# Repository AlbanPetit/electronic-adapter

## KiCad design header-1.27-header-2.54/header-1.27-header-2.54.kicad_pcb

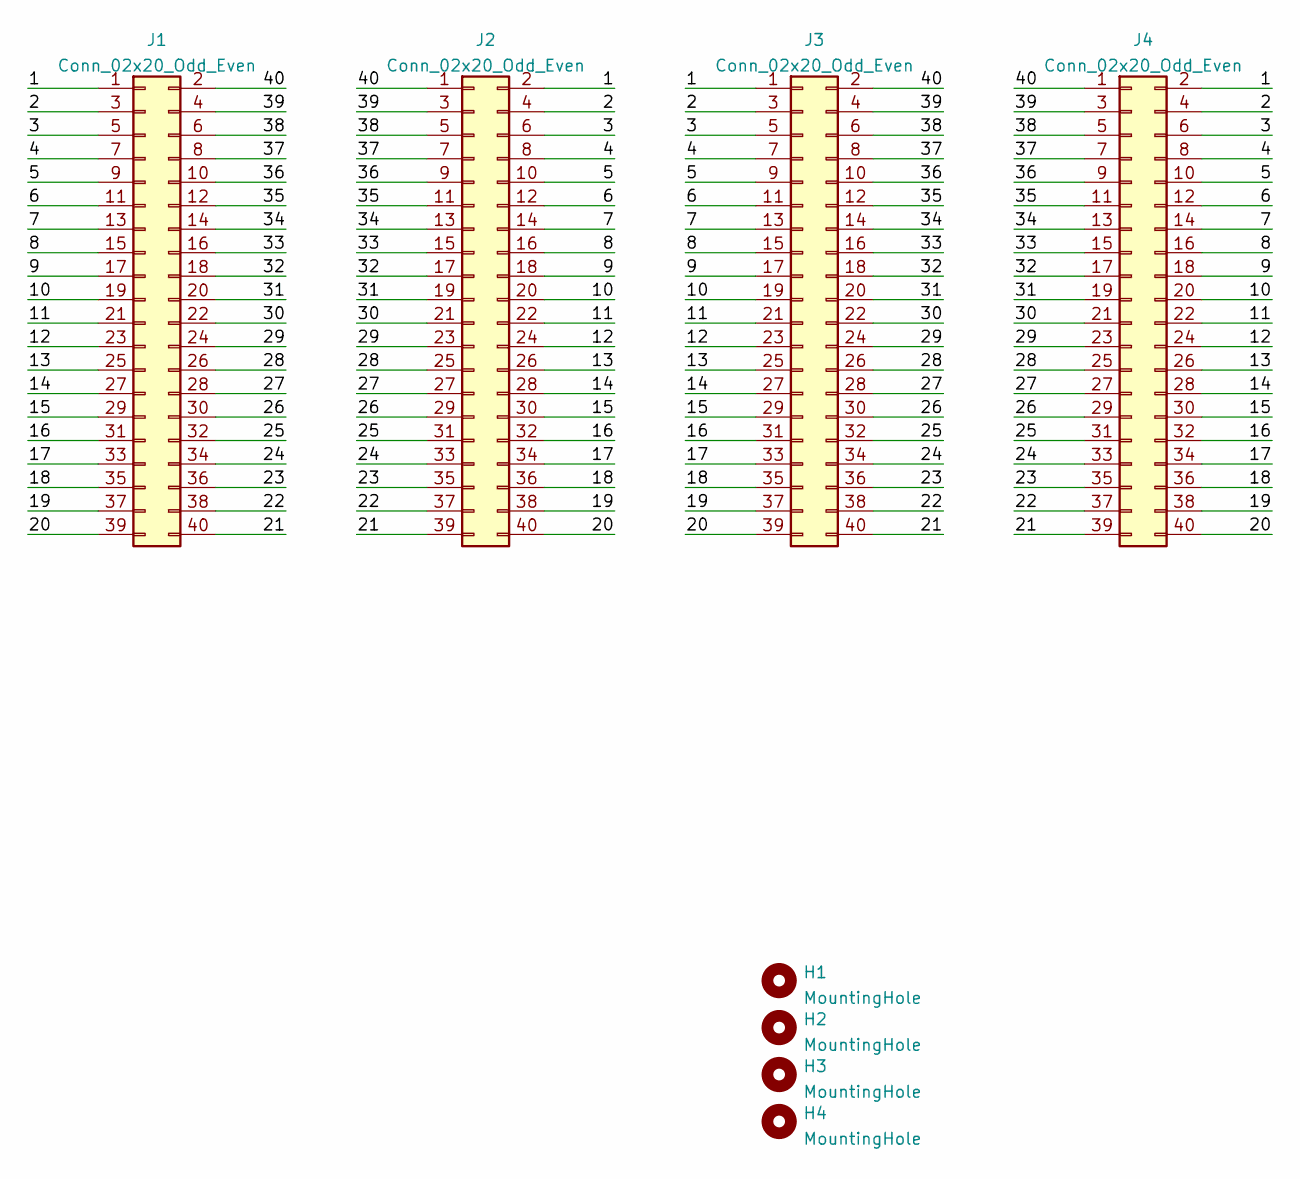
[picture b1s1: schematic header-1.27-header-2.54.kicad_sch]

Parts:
H1, H2, H3, H4: MountingHole; MountingHole_2.2mm_M2_DIN965_Pad
J1, J2: Conn_02x20_Odd_Even; PinHeader_2x20_P2.54mm_Vertical_SMD
J3, J4: Conn_02x20_Odd_Even; PinHeader_2x20_P1.27mm_Vertical_SMD

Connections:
/1: J1.1, J2.2, J3.1, J4.2
/2: J1.3, J2.4, J3.3, J4.4
/3: J1.5, J2.6, J3.5, J4.6
/4: J1.7, J2.8, J3.7, J4.8
/5: J1.9, J2.10, J3.9, J4.10
/6: J1.11, J2.12, J3.11, J4.12
/7: J1.13, J2.14, J3.13, J4.14
/8: J1.15, J2.16, J3.15, J4.16
/9: J1.17, J2.18, J3.17, J4.18
/10: J1.19, J2.20, J3.19, J4.20
/11: J1.21, J2.22, J3.21, J4.22
/12: J1.23, J2.24, J3.23, J4.24
/13: J1.25, J2.26, J3.25, J4.26
/14: J1.27, J2.28, J3.27, J4.28
/15: J1.29, J2.30, J3.29, J4.30
/16: J1.31, J2.32, J3.31, J4.32
/17: J1.33, J2.34, J3.33, J4.34
/18: J1.35, J2.36, J3.35, J4.36
/19: J1.37, J2.38, J3.37, J4.38
/20: J1.39, J2.40, J3.39, J4.40
/21: J1.40, J2.39, J3.40, J4.39
/22: J1.38, J2.37, J3.38, J4.37
/23: J1.36, J2.35, J3.36, J4.35
/24: J1.34, J2.33, J3.34, J4.33
/25: J1.32, J2.31, J3.32, J4.31
/26: J1.30, J2.29, J3.30, J4.29
/27: J1.28, J2.27, J3.28, J4.27
/28: J1.26, J2.25, J3.26, J4.25
/29: J1.24, J2.23, J3.24, J4.23
/30: J1.22, J2.21, J3.22, J4.21
/31: J1.20, J2.19, J3.20, J4.19
/32: J1.18, J2.17, J3.18, J4.17
/33: J1.16, J2.15, J3.16, J4.15
/34: J1.14, J2.13, J3.14, J4.13
/35: J1.12, J2.11, J3.12, J4.11
/36: J1.10, J2.9, J3.10, J4.9
/37: J1.8, J2.7, J3.8, J4.7
/38: J1.6, J2.5, J3.6, J4.5
/39: J1.4, J2.3, J3.4, J4.3
/40: J1.2, J2.1, J3.2, J4.1

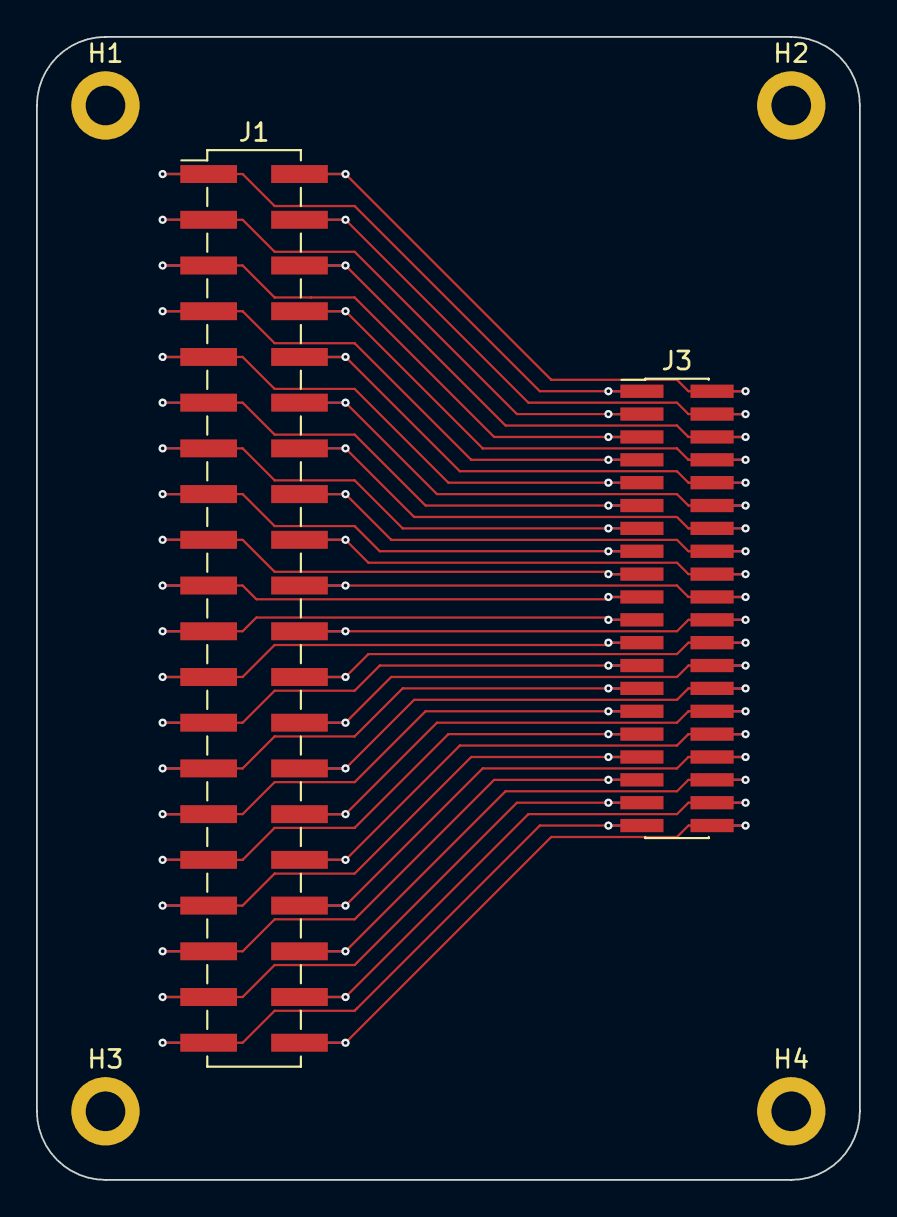
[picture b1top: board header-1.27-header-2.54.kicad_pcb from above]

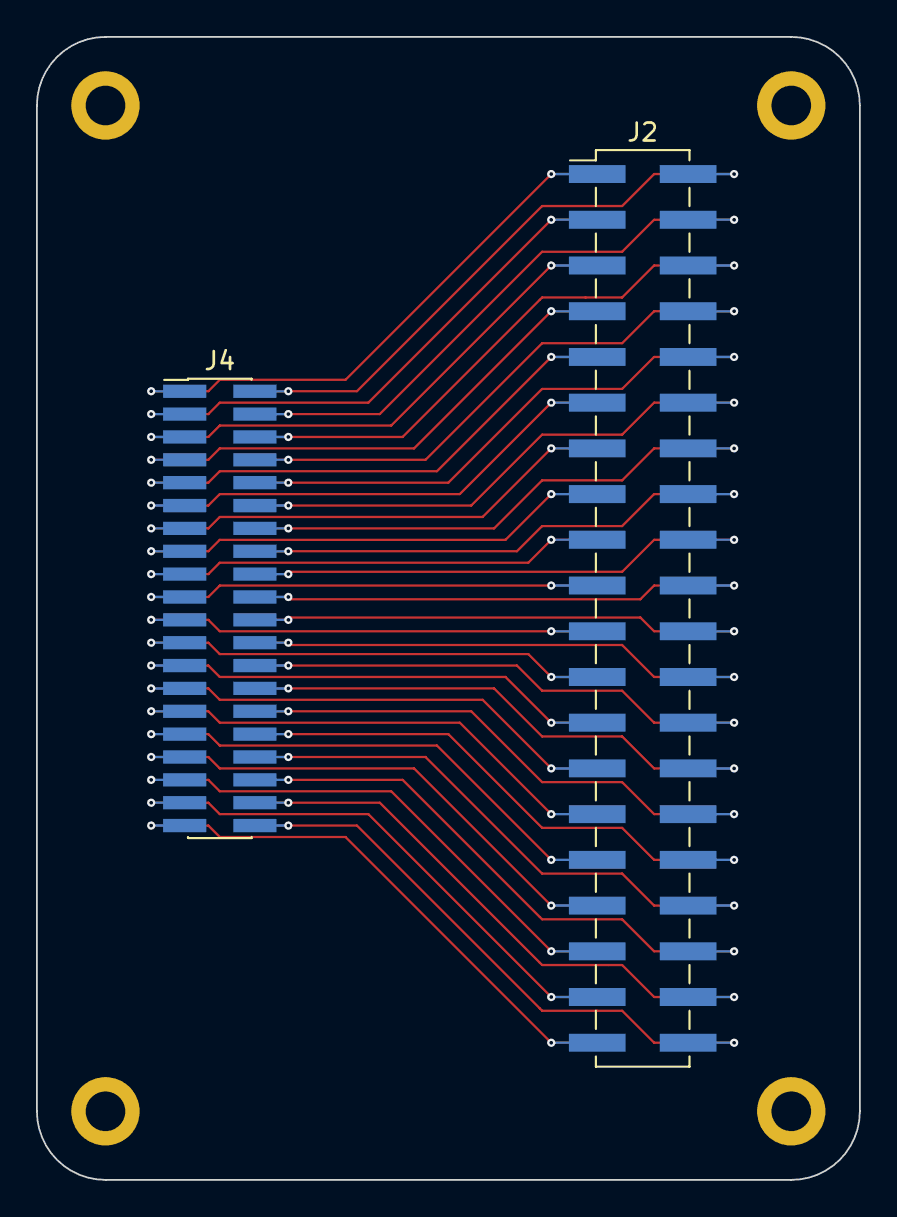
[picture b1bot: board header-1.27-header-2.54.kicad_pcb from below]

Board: 2 copper layers, 45.7 x 63.5 mm, 8 parts (2 on the bottom side), 40 nets.

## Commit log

2021-08-16 :tada: initial commit
